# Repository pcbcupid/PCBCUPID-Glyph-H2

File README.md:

# PCBCUPID-GLYPH-H2-PCB

This repo contains open source PCB files for PCBCUPID Glyph H2
This particular PCB is designed using Kicad v8.0

**This design has been built and tested successfully!**
For more details, check out the product pages at

   * [Glyph-H2](https://shop.pcbcupid.com/product/gd003/)

We are here to build India's largest open source hardware community, If you like to support
please consider buying the product from the above link!

[Creative Commons Attribution, Share-Alike license](https://creativecommons.org/licenses/by-sa/4.0/deed.en)
All text above must be included in any redistribution

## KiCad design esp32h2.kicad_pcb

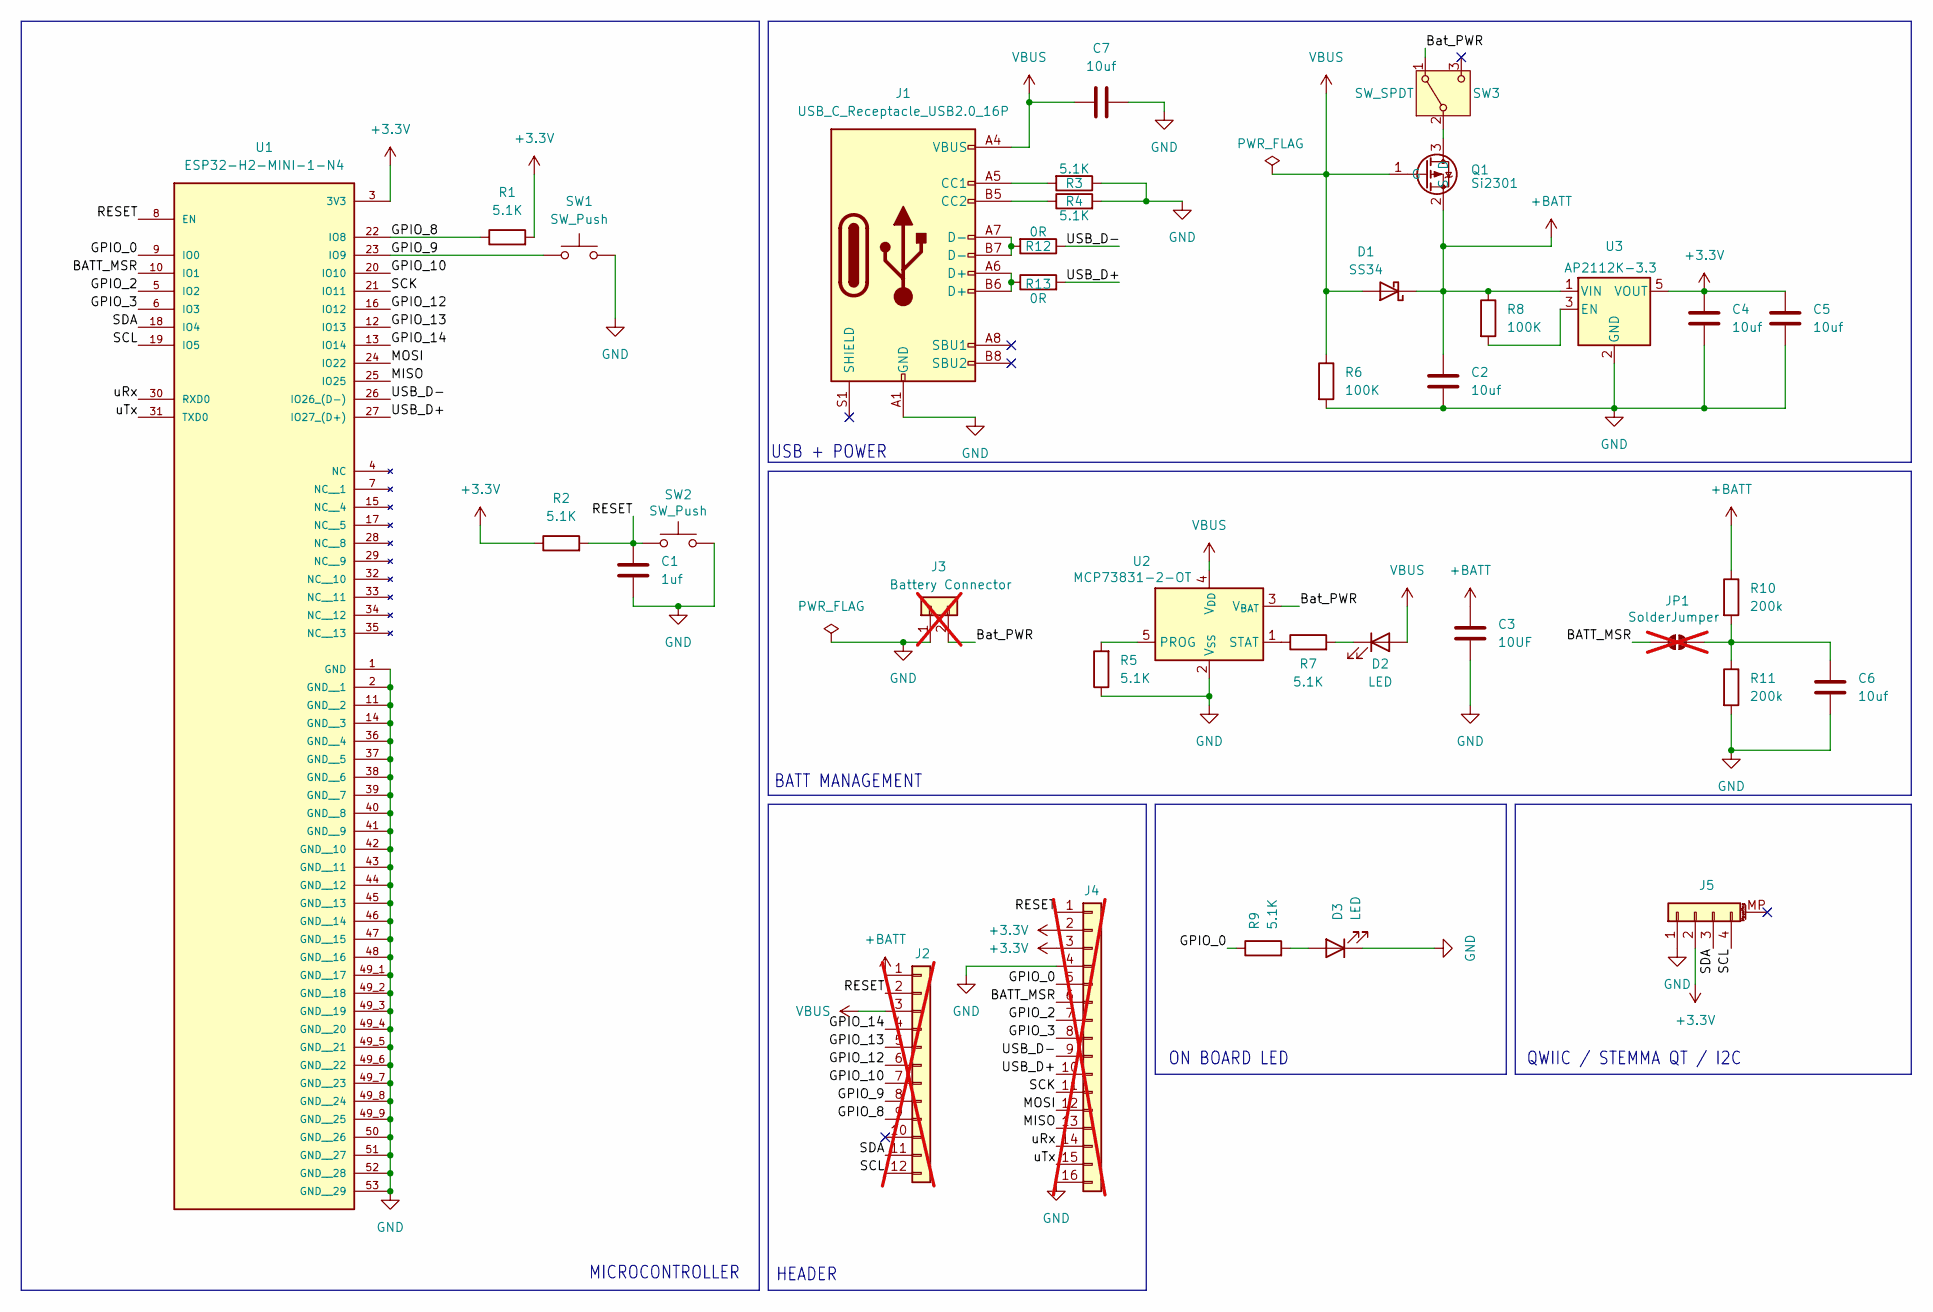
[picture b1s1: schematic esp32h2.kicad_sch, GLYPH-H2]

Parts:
C1: 1uf; C_0603_1608Metric
C2, C4, C5, C6, C7: 10uf; C_0603_1608Metric
C3: 10UF; C_0603_1608Metric
D1: SS34; D_SMA
D2, D3: LED; LED_0603_1608Metric
J1: USB_C_Receptacle_USB2.0_16P; USB_C_Receptacle_Palconn_UTC16-G
J2: Conn_01x12; PinSocket_1x12_P2.54mm_Vertical; not fitted
J3: Battery Connector; TestPoint_01x02; not fitted
J4: Conn_01x16; PinSocket_1x16_P2.54mm_Vertical; not fitted
J5: Conn_01x04_MountingPin; JST_SH_BM04B-SRSS-TB_1x04-1MP_P1.00mm_Vertical
JP1: SolderJumper; SolderJumper-2_P1.3mm_Open_RoundedPad1.0x1.5mm; not fitted
Q1: Si2301; SOT-23
R1, R2, R3, R4, R5, R7, R9: 5.1K; R_0603_1608Metric
R6, R8: 100K; R_0603_1608Metric
R10, R11: 200k; R_0603_1608Metric
R12, R13: 0R; R_0603_1608Metric
SW1, SW2: SW_Push; SW_SPST_PTS810
SW3: SW_SPDT; SW_SPDT_PCM12
U1: ESP32-H2-MINI-1-N4; ESP32-H2-MINI-1_EXP; PARTREV v1.0
U2: MCP73831-2-OT; SOT-23-5
U3: AP2112K-3.3; SOT-23-5

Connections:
+3.3V: C4.1, C5.1, J4.2, J4.3, J5.2, R1.2, R2.1, U1.3 (3V3), U3.5 (VOUT)
+BATT: C2.1, C3.1, D1.1 (K), J2.1, Q1.2 (S), R8.1, R10.1, U3.1 (VIN)
/BATT_MSR: J4.6, JP1.1 (A), U1.10 (IO1)
/Bat_PWR: J3.2, SW3.1 (A), U2.3 (V_{BAT})
/D+: J1.A6 (D+), J1.B6 (D+), R13.1
/D-: J1.A7 (D-), J1.B7 (D-), R12.2
/GPIO_0: J4.5, R9.1, U1.9 (IO0)
/GPIO_2: J4.7, U1.5 (IO2)
/GPIO_3: J4.8, U1.6 (IO3)
/GPIO_8: J2.9, R1.1, U1.22 (IO8)
/GPIO_9: J2.8, SW1.1, U1.23 (IO9)
/GPIO_10: J2.7, U1.20 (IO10)
/GPIO_12: J2.6, U1.16 (IO12)
/GPIO_13: J2.5, U1.12 (IO13)
/GPIO_14: J2.4, U1.13 (IO14)
/MISO: J4.13, U1.25 (IO25)
/MOSI: J4.12, U1.24 (IO22)
/RESET: C1.1, J2.2, J4.1, R2.2, SW2.1, U1.8 (EN)
/SCK: J4.11, U1.21 (IO11)
/SCL: J2.12, J5.4, U1.19 (IO5)
/SDA: J2.11, J5.3, U1.18 (IO4)
/USB_D+: J4.10, R13.2, U1.27 (IO27_(D+))
/USB_D-: J4.9, R12.1, U1.26 (IO26_(D-))
/uRx: J4.14, U1.30 (RXD0)
/uTx: J4.15, U1.31 (TXD0)
GND: C1.2, C2.2, C3.2, C4.2, C5.2, C6.2, C7.2, D3.1 (K), J1.A1 (GND), J1.A12 (GND), J1.B1 (GND), J1.B12 (GND), J3.1, J4.4, J4.16, J5.1, R3.1, R4.2, R5.1, R6.2, R11.2, SW1.2, SW2.2, U1.1 (GND), U1.2 (GND__1), U1.11 (GND__2), U1.14 (GND__3), U1.36 (GND__4), U1.37 (GND__5), U1.38 (GND__6), U1.39 (GND__7), U1.40 (GND__8), U1.41 (GND__9), U1.42 (GND__10), U1.43 (GND__11), U1.44 (GND__12), U1.45 (GND__13), U1.46 (GND__14), U1.47 (GND__15), U1.48 (GND__16), U1.49_1 (GND__17), U1.49_2 (GND__18), U1.49_3 (GND__19), U1.49_4 (GND__20), U1.49_5 (GND__21), U1.49_6 (GND__22), U1.49_7 (GND__23), U1.49_8 (GND__24), U1.49_9 (GND__25), U1.50 (GND__26), U1.51 (GND__27), U1.52 (GND__28), U1.53 (GND__29), U2.2 (V_{SS}), U3.2 (GND)
unnamed: D2.1 (K), R7.2
unnamed: D3.2 (A), R9.2
unnamed: J1.A5 (CC1), R3.2
unnamed: J1.B5 (CC2), R4.1
unnamed: C6.1, JP1.2 (B), R10.2, R11.1
unnamed: Q1.3 (D), SW3.2 (B)
unnamed: R5.2, U2.5 (PROG)
unnamed: R7.1, U2.1 (STAT)
unnamed: R8.2, U3.3 (EN)
VBUS: C7.1, D1.2 (A), D2.2 (A), J1.A4 (VBUS), J1.A9 (VBUS), J1.B4 (VBUS), J1.B9 (VBUS), J2.3, Q1.1 (G), R6.1, U2.4 (V_{DD})

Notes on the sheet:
ON BOARD LED
HEADER
BATT MANAGEMENT
QWIIC / STEMMA QT / I2C
MICROCONTROLLER
USB + POWER

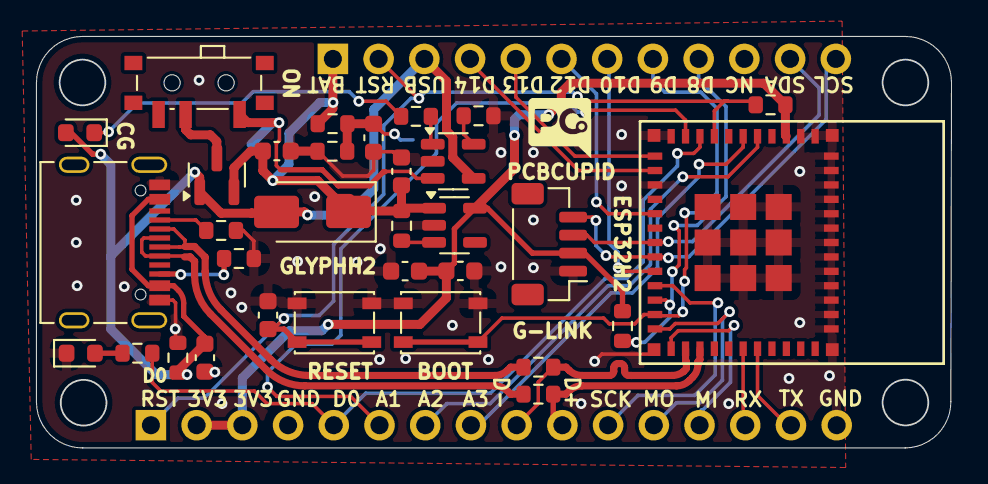
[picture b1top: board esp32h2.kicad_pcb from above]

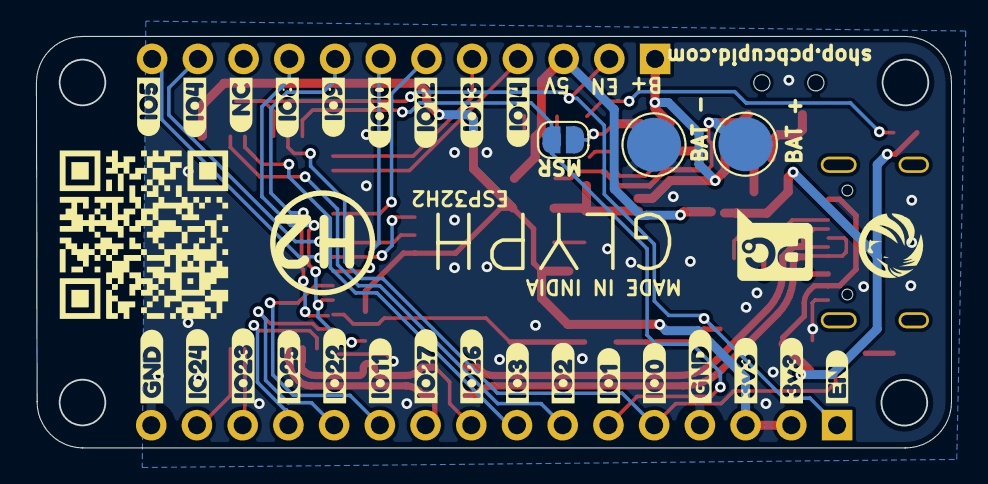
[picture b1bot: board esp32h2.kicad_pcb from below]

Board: 2 copper layers, 50.8 x 22.8 mm, 61 parts (28 on the bottom side), 36 nets.

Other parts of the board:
kibuzzard-668B7A0A: G***; kibuzzard-668B7A0A
kibuzzard-668B7A1E: G***; kibuzzard-668B7A1E
kibuzzard-668B7A2D: G***; kibuzzard-668B7A2D
kibuzzard-668B7A7C: G***; kibuzzard-668B7A7C
kibuzzard-668B7A62, kibuzzard-668B7A62#2: G***; kibuzzard-668B7A62
kibuzzard-668B79F7: G***; kibuzzard-668B79F7
kibuzzard-668B789B, kibuzzard-668B789B#2: G***; kibuzzard-668B789B
kibuzzard-668CCB9F: G***; kibuzzard-668CCB9F
kibuzzard-668CCB83: G***; kibuzzard-668CCB83
kibuzzard-668CEB4E: G***; kibuzzard-668CEB4E
kibuzzard-668CEB46: G***; kibuzzard-668CEB46
kibuzzard-668CEBAF: G***; kibuzzard-668CEBAF
kibuzzard-668CEBCF: G***; kibuzzard-668CEBCF
kibuzzard-668CEBDE: G***; kibuzzard-668CEBDE
kibuzzard-668CEBE8: G***; kibuzzard-668CEBE8
kibuzzard-668CEBF5: G***; kibuzzard-668CEBF5
kibuzzard-668CED4F: G***; kibuzzard-668CED4F
kibuzzard-668CED5D: G***; kibuzzard-668CED5D
kibuzzard-668CED41: G***; kibuzzard-668CED41
kibuzzard-668CED68: G***; kibuzzard-668CED68
kibuzzard-668CED74: G***; kibuzzard-668CED74
kibuzzard-668CED78: G***; kibuzzard-668CED78
kibuzzard-668CED80: G***; kibuzzard-668CED80

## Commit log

2024-09-05 Release v1.0.0
2024-09-05 added read.me

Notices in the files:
esp32h2.kicad_sch:
License : CC-BY-SA
